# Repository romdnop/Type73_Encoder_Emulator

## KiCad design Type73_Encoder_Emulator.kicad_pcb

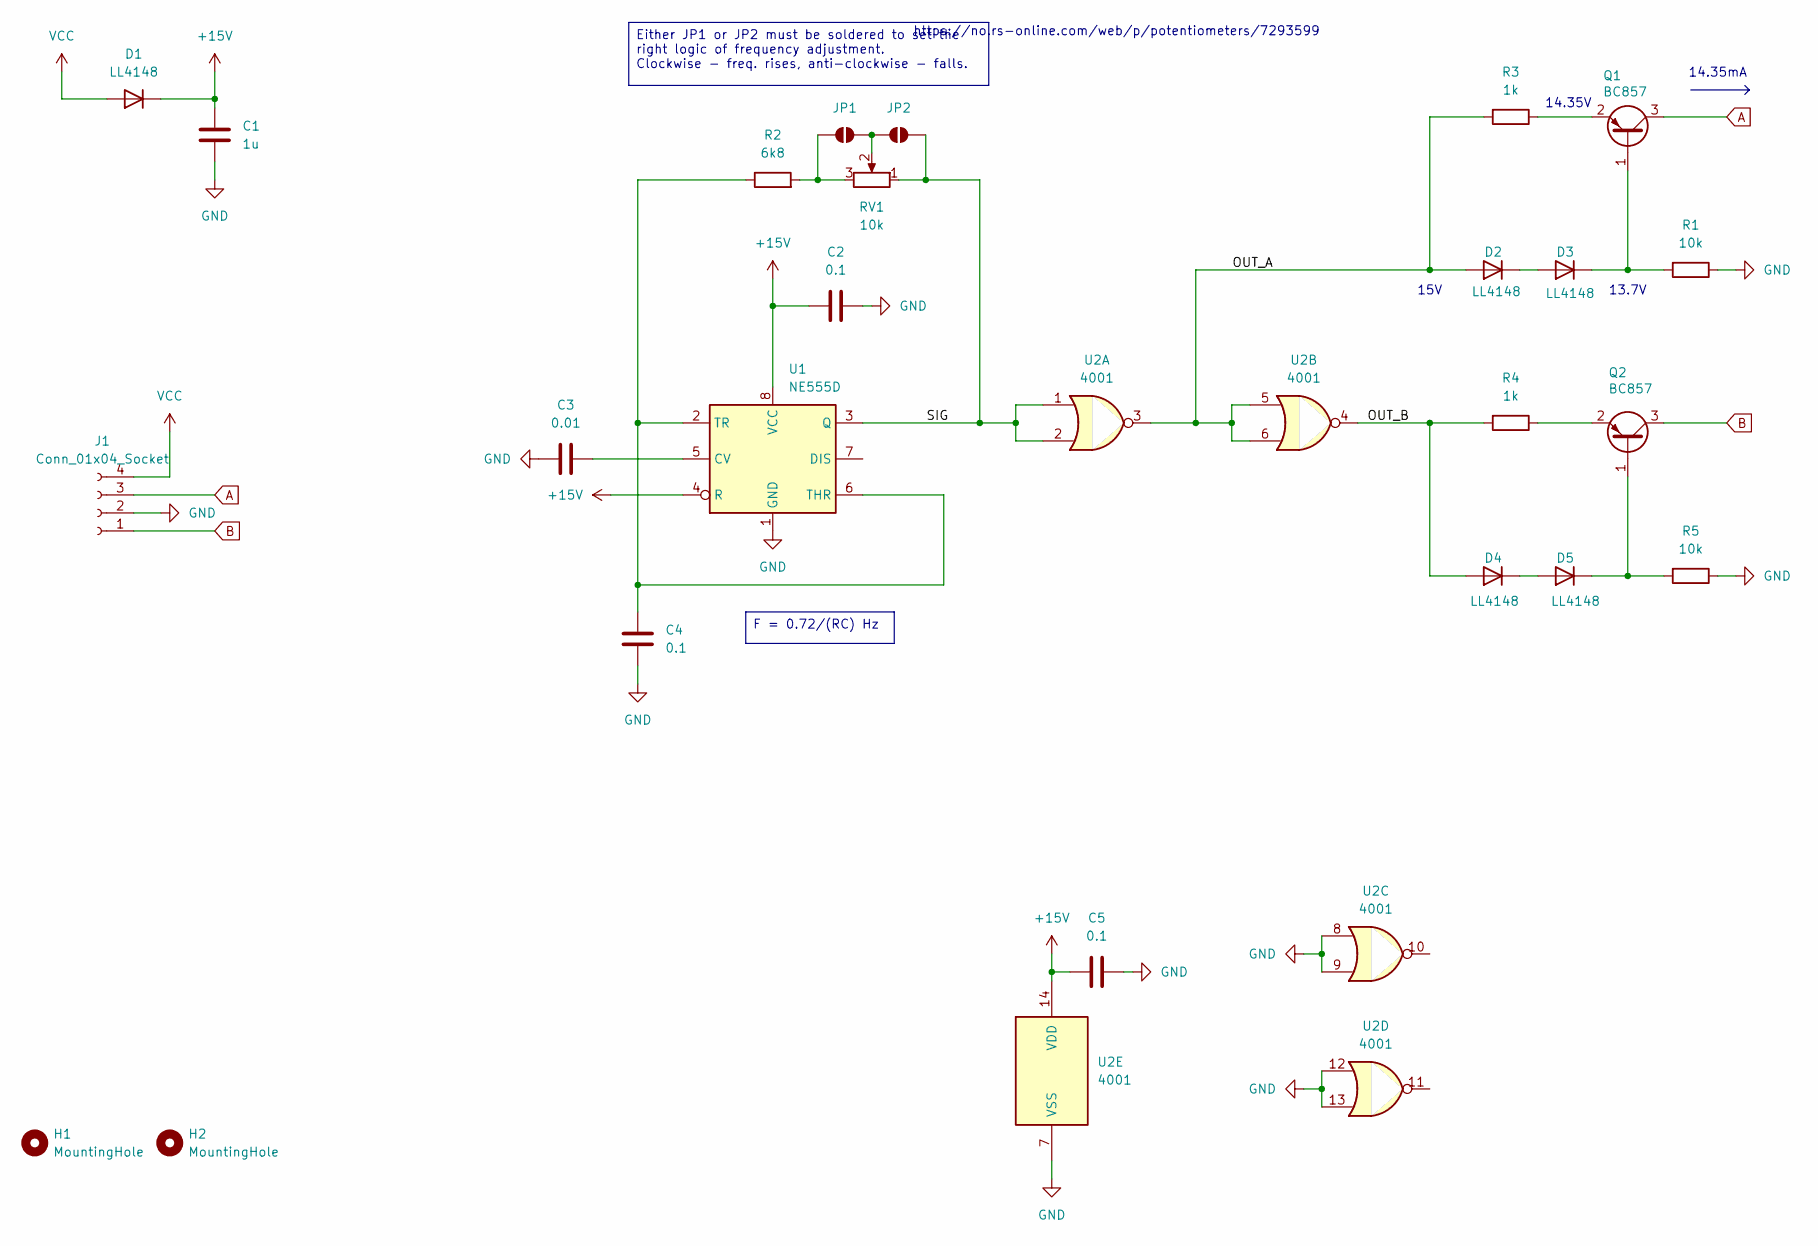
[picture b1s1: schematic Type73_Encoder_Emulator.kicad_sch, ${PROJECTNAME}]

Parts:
C1: 1u; C_1206_3216Metric
C2, C4, C5: 0.1; C_0805_2012Metric
C3: 0.01; C_0805_2012Metric
D1, D2, D3, D4, D5: LL4148; D_MiniMELF
H1, H2: MountingHole; MountingHole_2.5mm
J1: Conn_01x04_Socket; PinSocket_1x04_P2.54mm_Vertical
JP1, JP2: SolderJumper_2_Open; SolderJumper-2_P1.3mm_Open_RoundedPad1.0x1.5mm
Q1, Q2: BC857; SOT-23
R1, R5: 10k; R_0805_2012Metric
R2: 6k8; R_0805_2012Metric
R3, R4: 1k; R_0805_2012Metric
RV1: 10k; Potentiometer_Alps_RK09K_Single_Vertical
U1: NE555D; SOIC-8_3.9x4.9mm_P1.27mm
U2: 4001; SO-14_3.9x8.65mm_P1.27mm

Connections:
+15V: C1.1, C2.1, C5.1, D1.1 (K), U1.4 (R), U1.8 (VCC), U2.14 (VDD)
/OUT_A: D2.2 (A), R3.2, U2.3, U2.5, U2.6
/OUT_B: D4.2 (A), R4.2, U2.4
/SIG: JP2.2 (B), RV1.1, U1.3 (Q), U2.1, U2.2
A: J1.3, Q1.3 (C)
B: J1.1, Q2.3 (C)
GND: C1.2, C2.2, C3.1, C4.1, C5.2, J1.2, R1.1, R5.1, U1.1 (GND), U2.7 (VSS), U2.8, U2.9, U2.12, U2.13
unnamed: D2.1 (K), D3.2 (A)
unnamed: D3.1 (K), Q1.1 (B), R1.2
unnamed: D4.1 (K), D5.2 (A)
unnamed: D5.1 (K), Q2.1 (B), R5.2
unnamed: JP1.1 (A), R2.2, RV1.3
unnamed: JP1.2 (B), JP2.1 (A), RV1.2
unnamed: Q1.2 (E), R3.1
unnamed: Q2.2 (E), R4.1
unnamed: C3.2, U1.5 (CV)
unnamed: C4.2, R2.1, U1.2 (TR), U1.6 (THR)
VCC: D1.2 (A), J1.4

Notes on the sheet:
https://no.rs-online.com/web/p/potentiometers/7293599
13.7V
14.35V
15V
14.35mA
F = 0.72/(RC) Hz
Either JP1 or JP2 must be soldered to set the right logic of frequency adjustment. Clockwise - freq. rises, anti-clockwise - falls.

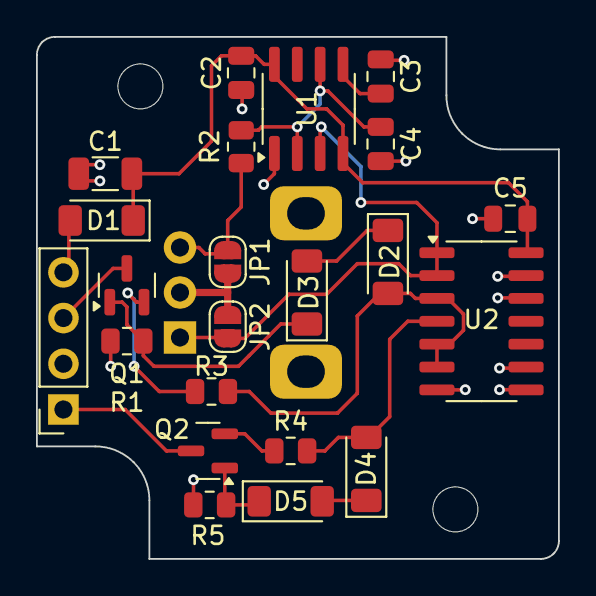
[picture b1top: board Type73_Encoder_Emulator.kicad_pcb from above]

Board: 2 copper layers, 29.0 x 29.0 mm, 25 parts (1 on the bottom side), 18 nets.

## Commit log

2026-03-01 Re-arranged silkscreen elements
2026-03-02 Fixed backslash problem in output files generation
